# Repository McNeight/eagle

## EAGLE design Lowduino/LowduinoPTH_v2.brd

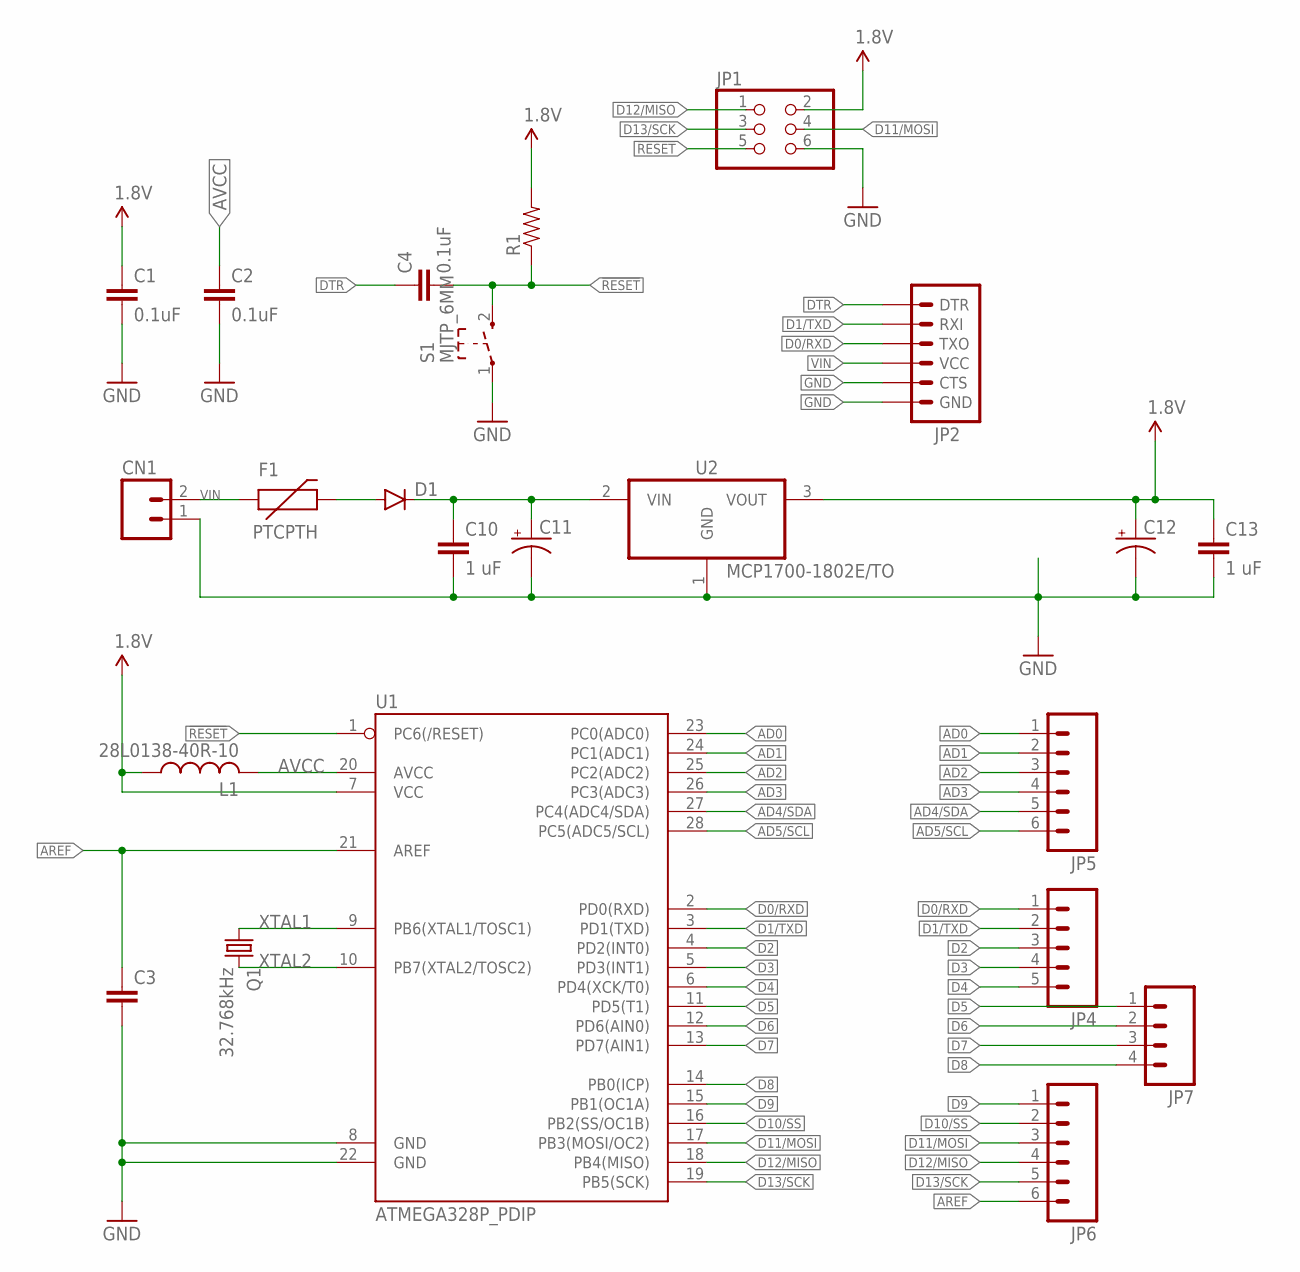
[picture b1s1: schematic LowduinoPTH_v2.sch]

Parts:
C1, C4: 0.1uF; CAP-PTH-SMALL
C2: 0.1uF; CAP-PTH-5MM
C3: CAPPTH; CAP-PTH-SMALL
C10, C13: 1 uF; CAP-PTH-SMALL
C11, C12: CPOL-USE2.5-6; E2,5-6
CN1: M02JST-PTH-VERT; JST-2-PTH-VERT
D1: DIODEPTH; DIODE-1N4001
F1: PTCPTH; PTC
JP1: PINHD-2X3; 2X03
JP2: ARDUINO_SERIAL_PROGRAMPTH; 1X06
JP4: M05NO_SILK; 1X05_NO_SILK
JP5, JP6: M06NO_SILK_FEMALE_PTH; 1X06_NO_SILK
JP7: M04NO_SILK_ALL_ROUND; 1X04_NO_SILK_ALL_ROUND
L1: 28L0138-40R-10; LAL03
Q1: 32.768kHz; TC26V
R1: RESISTORPTH-1/4W-VERT; AXIAL-0.1
S1: MJTP_6MM; MJTP1243
U1: ATMEGA328P_PDIP; DIL28-3
U2: MCP1700-1802E/TO; MICROCHIP_TO

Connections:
1.8V: C1.1, C12.+, C13.1, JP1.2, L1.1, R1.P$2 (2), U1.7 (VCC), U2.3 (VOUT)
!RESET: C4.2, JP1.5, R1.P$1 (1), S1.2 (3), U1.1 (PC6(/RESET))
AD0: JP5.1, U1.23 (PC0(ADC0))
AD1: JP5.2, U1.24 (PC1(ADC1))
AD2: JP5.3, U1.25 (PC2(ADC2))
AD3: JP5.4, U1.26 (PC3(ADC3))
AD4/SDA: JP5.5, U1.27 (PC4(ADC4/SDA))
AD5/SCL: JP5.6, U1.28 (PC5(ADC5/SCL))
AREF: C3.1, JP6.6, U1.21 (AREF)
AVCC: C2.1, L1.2, U1.20 (AVCC)
D0/RXD: JP2.3 (TXO), JP4.1, U1.2 (PD0(RXD))
D1/TXD: JP2.2 (RXI), JP4.2, U1.3 (PD1(TXD))
D2: JP4.3, U1.4 (PD2(INT0))
D3: JP4.4, U1.5 (PD3(INT1))
D4: JP4.5, U1.6 (PD4(XCK/T0))
D5: JP7.1, U1.11 (PD5(T1))
D6: JP7.2, U1.12 (PD6(AIN0))
D7: JP7.3, U1.13 (PD7(AIN1))
D8: JP7.4, U1.14 (PB0(ICP))
D9: JP6.1, U1.15 (PB1(OC1A))
D10/SS: JP6.2, U1.16 (PB2(SS/OC1B))
D11/MOSI: JP1.4, JP6.3, U1.17 (PB3(MOSI/OC2))
D12/MISO: JP1.1, JP6.4, U1.18 (PB4(MISO))
D13/SCK: JP1.3, JP6.5, U1.19 (PB5(SCK))
DTR: C4.1, JP2.1 (DTR)
GND: C1.2, C2.2, C3.2, C10.2, C11.-, C12.-, C13.2, CN1.1, JP1.6, JP2.5 (CTS), JP2.6 (GND), S1.1, U1.8 (GND), U1.22 (GND), U2.1 (GND)
unnamed: D1.A, F1.P$2 (2)
unnamed: C10.1, C11.+, D1.C, U2.2 (VIN)
VIN: CN1.2, F1.P$1 (1), JP2.4 (VCC)
XTAL1: Q1.1, U1.9 (PB6(XTAL1/TOSC1))
XTAL2: Q1.2, U1.10 (PB7(XTAL2/TOSC2))

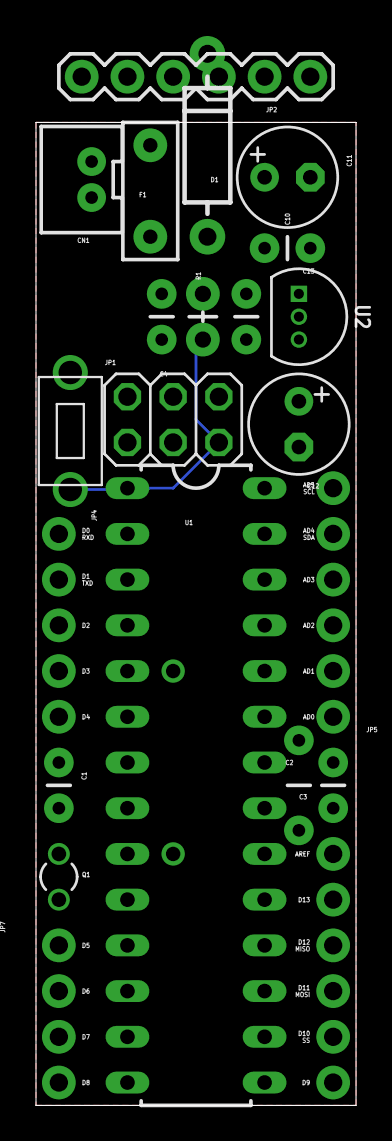
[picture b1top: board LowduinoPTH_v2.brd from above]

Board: 2 copper layers, 17.8 x 54.6 mm, 23 parts (1 on the bottom side), 31 nets.

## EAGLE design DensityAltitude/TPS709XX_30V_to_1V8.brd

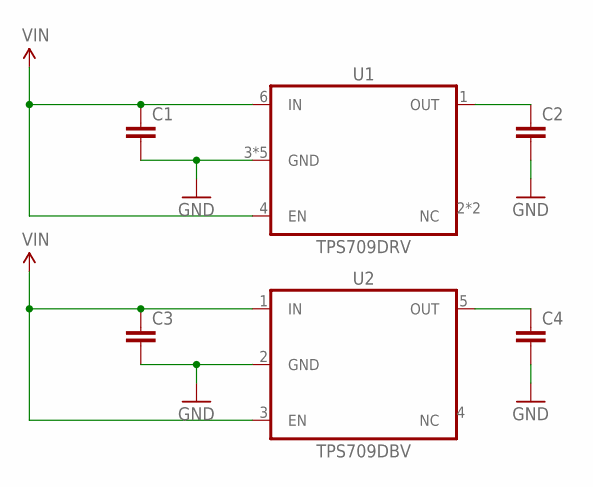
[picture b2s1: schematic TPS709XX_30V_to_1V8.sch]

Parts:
C1, C2: C-EUC0402; C0402
C3, C4: C-EUC0603; C0603
U1: TPS709DRV; DRV
U2: TPS709DBV; DBV

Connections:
GND: C1.2, C2.2, C3.2, C4.2, U1.3 (GND), U1.7 (GND), U1.8 (GND), U1.V1 (GND), U1.V2 (GND), U2.2 (GND)
VIN: C1.1, C3.1, U1.4 (EN), U1.6 (IN), U2.1 (IN), U2.3 (EN)
VOUT1: C2.1, U1.1 (OUT)
VOUT2: C4.1, U2.5 (OUT)

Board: 2 copper layers, 6 parts (0 on the bottom side), 4 nets, no tracks yet.

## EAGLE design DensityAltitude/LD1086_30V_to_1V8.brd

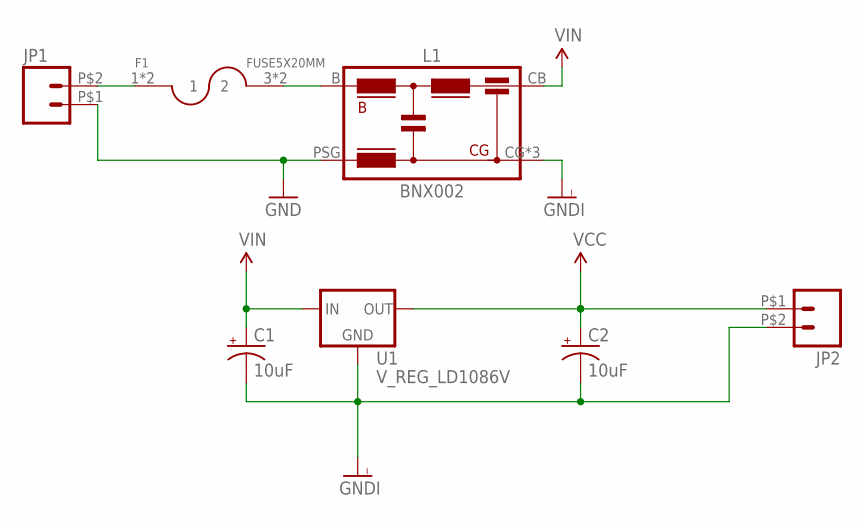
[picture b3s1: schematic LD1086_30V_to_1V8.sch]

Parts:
C1, C2: 10uF; KEMET_E
F1: FUSE5X20MM; FUSE_1A3399
JP1, JP2: M02TE-282834-2; 1X02_282834-2
L1: BNX002
U1: V_REG_LD1086V; TO-220-SINGLE

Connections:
GND: JP1.P$1 (1), L1.PSG
GNDI: C1.-, C2.-, JP2.P$2 (2), L1.CG, L1.CG1 (CG), L1.CG2 (CG), U1.GND
unnamed: F1.3 (2), F1.4 (2), L1.B
unnamed: F1.1, F1.2 (1), JP1.P$2 (2)
VCC: C2.+, JP2.P$1 (1), U1.OUT
VIN: C1.+, L1.CB, U1.IN

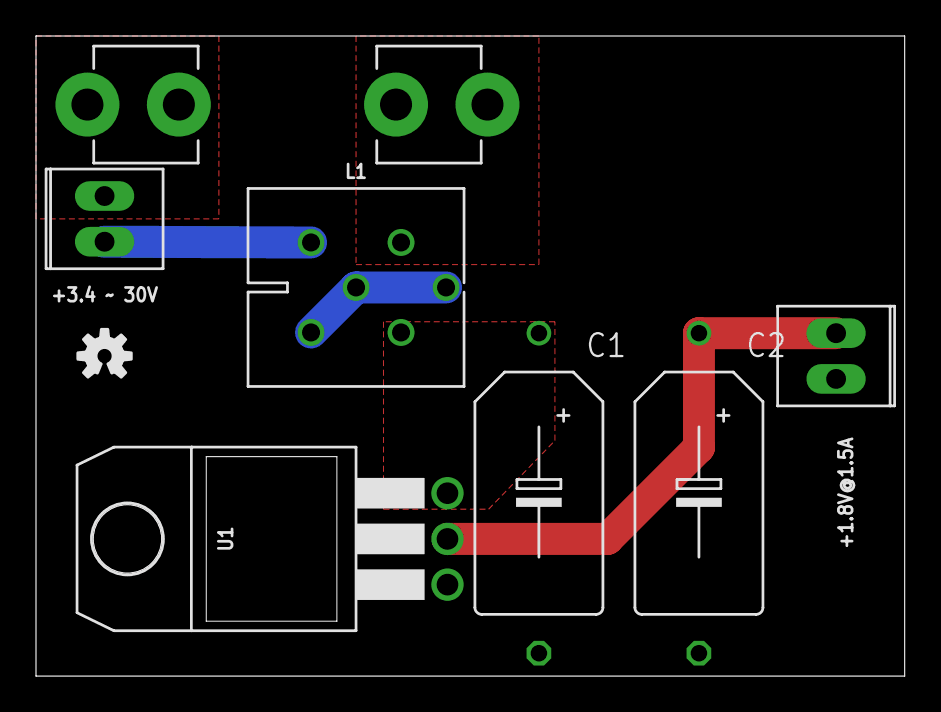
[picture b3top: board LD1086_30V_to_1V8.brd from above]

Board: 2 copper layers, 48.3 x 35.6 mm, 8 parts (0 on the bottom side), 6 nets.

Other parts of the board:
U$1: OSHW-LOGO-S

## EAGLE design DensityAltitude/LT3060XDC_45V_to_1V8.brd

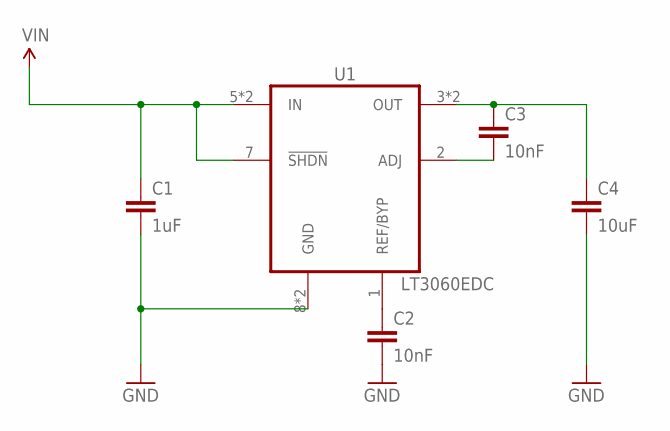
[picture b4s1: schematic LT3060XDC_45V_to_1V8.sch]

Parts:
C1: 1uF; C0402
C2, C3: 10nF; C0402
C4: 10uF; C0402
U1: LT3060EDC; LINEAR_DC8

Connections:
GND: C1.2, C2.2, C4.2, U1.8 (GND), U1.9 (GND)
unnamed: C3.2, U1.2 (ADJ)
unnamed: C2.1, U1.1 (REF/BYP)
OUT: C3.1, C4.1, U1.3 (OUT), U1.4 (OUT)
VIN: C1.1, U1.5 (IN), U1.6 (IN), U1.7 (!SHDN)

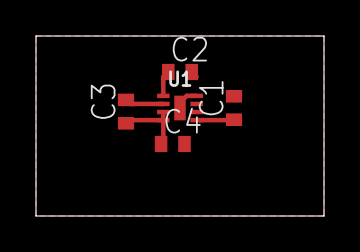
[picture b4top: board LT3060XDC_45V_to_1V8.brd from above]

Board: 2 copper layers, 16.0 x 10.0 mm, 5 parts (0 on the bottom side), 5 nets.

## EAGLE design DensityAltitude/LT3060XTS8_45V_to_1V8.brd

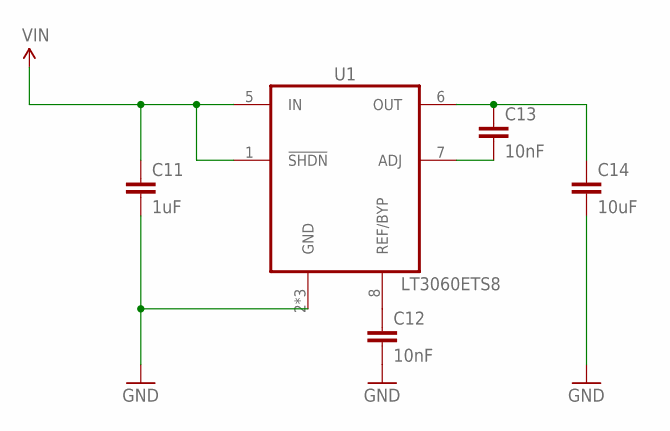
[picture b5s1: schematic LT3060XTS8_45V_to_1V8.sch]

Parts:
C11: 1uF; C0402
C12, C13: 10nF; C0402
C14: 10uF; C0402
U1: LT3060ETS8; LINEAR_TS8

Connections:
GND: C11.2, C12.2, C14.2, U1.2 (GND), U1.3 (GND), U1.4 (GND)
unnamed: C13.2, U1.7 (ADJ)
unnamed: C12.1, U1.8 (REF/BYP)
OUT: C13.1, C14.1, U1.6 (OUT)
VIN: C11.1, U1.1 (!SHDN), U1.5 (IN)

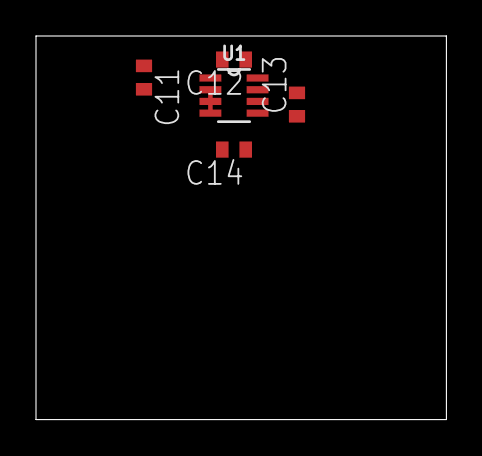
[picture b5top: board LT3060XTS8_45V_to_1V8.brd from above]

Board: 2 copper layers, 22.8 x 21.3 mm, 5 parts (0 on the bottom side), 5 nets.

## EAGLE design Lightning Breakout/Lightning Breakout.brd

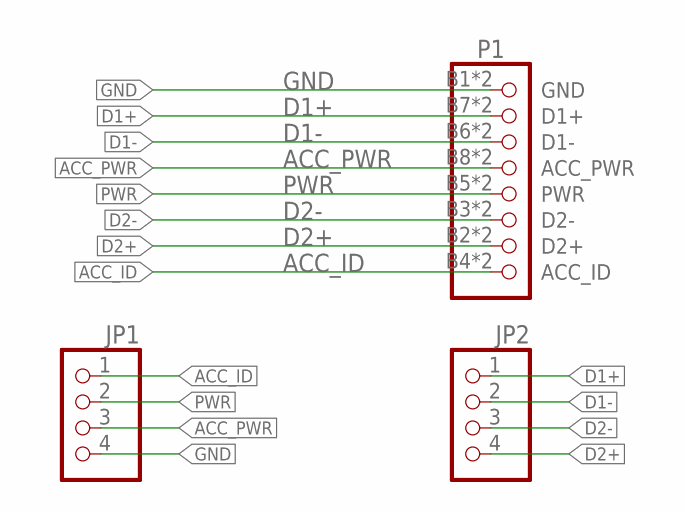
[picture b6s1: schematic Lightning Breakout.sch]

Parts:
JP1, JP2: PINHD-1X4; 1X04
P1: LIGHTNING-8PIN; LIGHTNING

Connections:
ACC_ID: JP1.1, P1.B4 (ACC_ID), P1.T8 (ACC_ID)
ACC_PWR: JP1.3, P1.B8 (ACC_PWR), P1.T4 (ACC_PWR)
D1+: JP2.1, P1.B7 (D1+), P1.T2 (D1+)
D1-: JP2.2, P1.B6 (D1-), P1.T3 (D1-)
D2+: JP2.4, P1.B2 (D2+), P1.T7 (D2+)
D2-: JP2.3, P1.B3 (D2-), P1.T6 (D2-)
GND: JP1.4, P1.B1 (GND), P1.T1 (GND)
PWR: JP1.2, P1.B5 (PWR), P1.T5 (PWR)

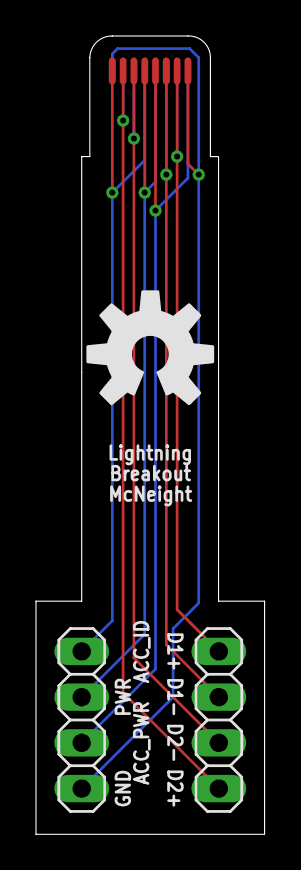
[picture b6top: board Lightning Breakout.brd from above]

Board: 2 copper layers, 12.7 x 44.4 mm, 4 parts (0 on the bottom side), 8 nets.

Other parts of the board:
U$1: OSHW-LOGO-L

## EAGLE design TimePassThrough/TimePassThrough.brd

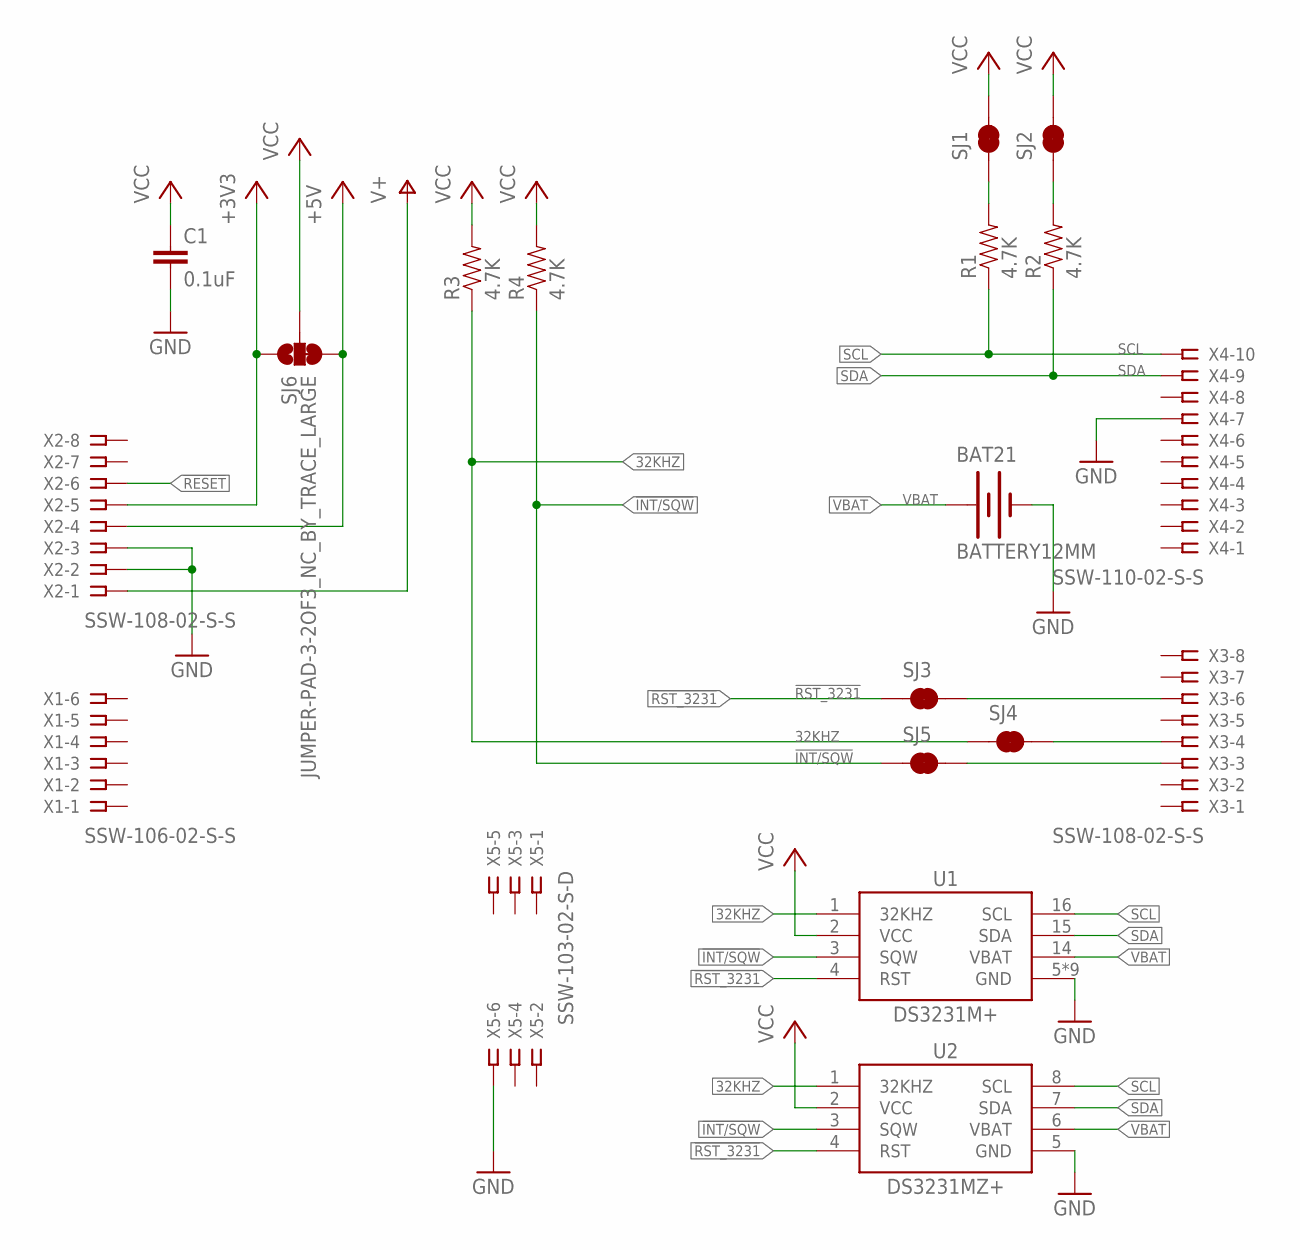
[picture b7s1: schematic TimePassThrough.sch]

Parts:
BAT21: BATTERY12MM; BATTCON_12MM
C1: 0.1uF; 0805
R1, R2, R3, R4: 4.7K; 0805
SJ1, SJ2, SJ3, SJ4, SJ5: JUMPER-PAD-2-NC_BY_TRACE; PAD-JUMPER-2-NC_BY_TRACE_YES_SILK
SJ6: JUMPER-PAD-3-2OF3_NC_BY_TRACE_LARGE; PAD-JUMPER-3-2OF3_NC_BY_TRACE_YES_SILK_LARGE
U1: DS3231M+; W16MK+1
U2: DS3231MZ+; S8MK+1
X1: SSW-106-02-S-S
X2, X3: SSW-108-02-S-S
X4: SSW-110-02-S-S
X5: SSW-103-02-S-D

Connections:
32KHZ: R3.1, SJ4.1, U1.1 (32KHZ), U2.1 (32KHZ)
!INT/SQW: R4.1, SJ5.1, U1.3 (SQW), U2.3 (SQW)
!RESET: X2.6
!RST_3231: SJ3.1, U1.4 (RST), U2.4 (RST)
+3V3: SJ6.1, X2.5
+5V: SJ6.3, X2.4
GND: BAT21.GND (-), C1.2, U1.5 (GND), U1.6 (GND), U1.7 (GND), U1.8 (GND), U1.9 (GND), U1.10 (GND), U1.11 (GND), U1.12 (GND), U1.13 (GND), U2.5 (GND), X2.2, X2.3, X4.7, X5.6
unnamed: SJ3.2, X3.6
unnamed: SJ4.2, X3.4
unnamed: SJ5.2, X3.3
unnamed: R1.2, SJ1.1
unnamed: R2.2, SJ2.1
SCL: R1.1, U1.16 (SCL), U2.8 (SCL), X4.10
SDA: R2.1, U1.15 (SDA), U2.7 (SDA), X4.9
V+: X2.1
VBAT: BAT21.PWR@1 (+), BAT21.PWR@2 (+), U1.14 (VBAT), U2.6 (VBAT)
VCC: C1.1, R3.2, R4.2, SJ1.2, SJ2.2, SJ6.2, U1.2 (VCC), U2.2 (VCC)

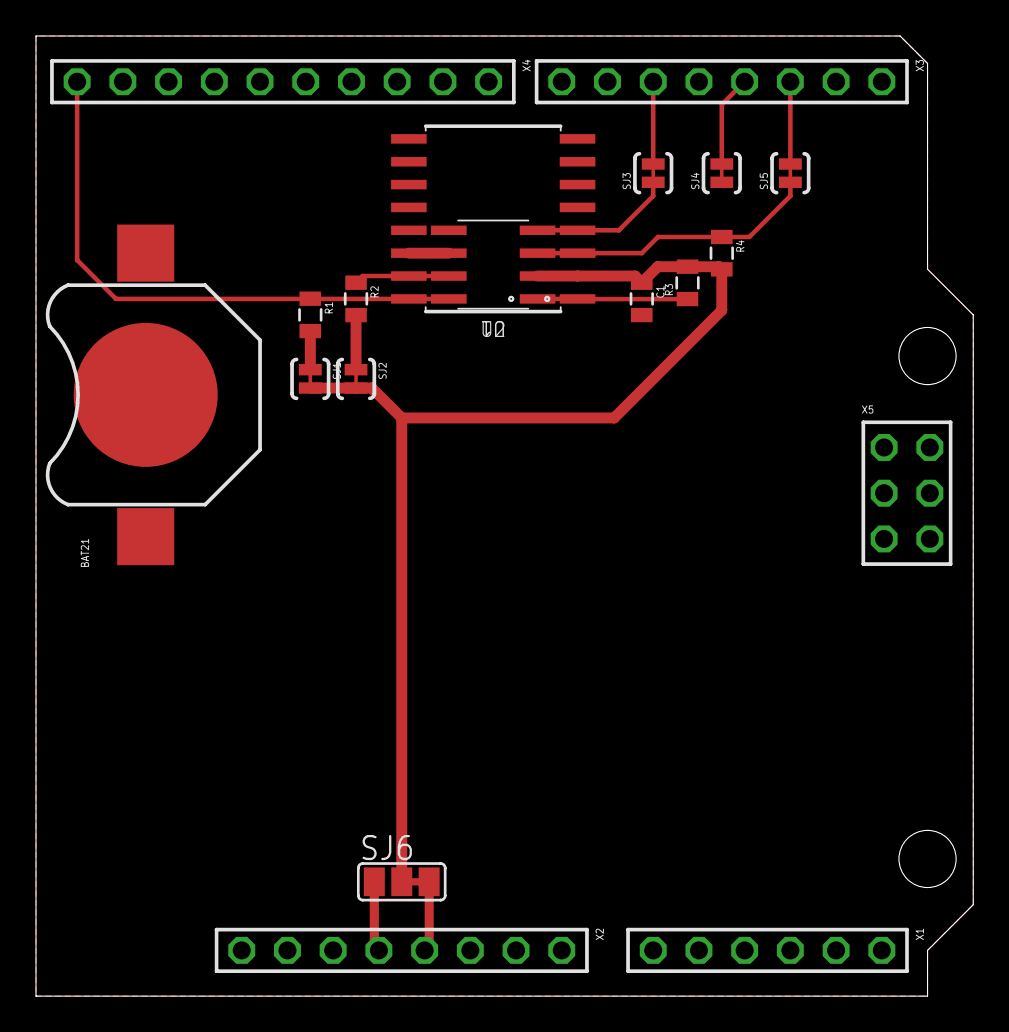
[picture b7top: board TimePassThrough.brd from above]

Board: 2 copper layers, 52.1 x 53.3 mm, 19 parts (0 on the bottom side), 15 nets.

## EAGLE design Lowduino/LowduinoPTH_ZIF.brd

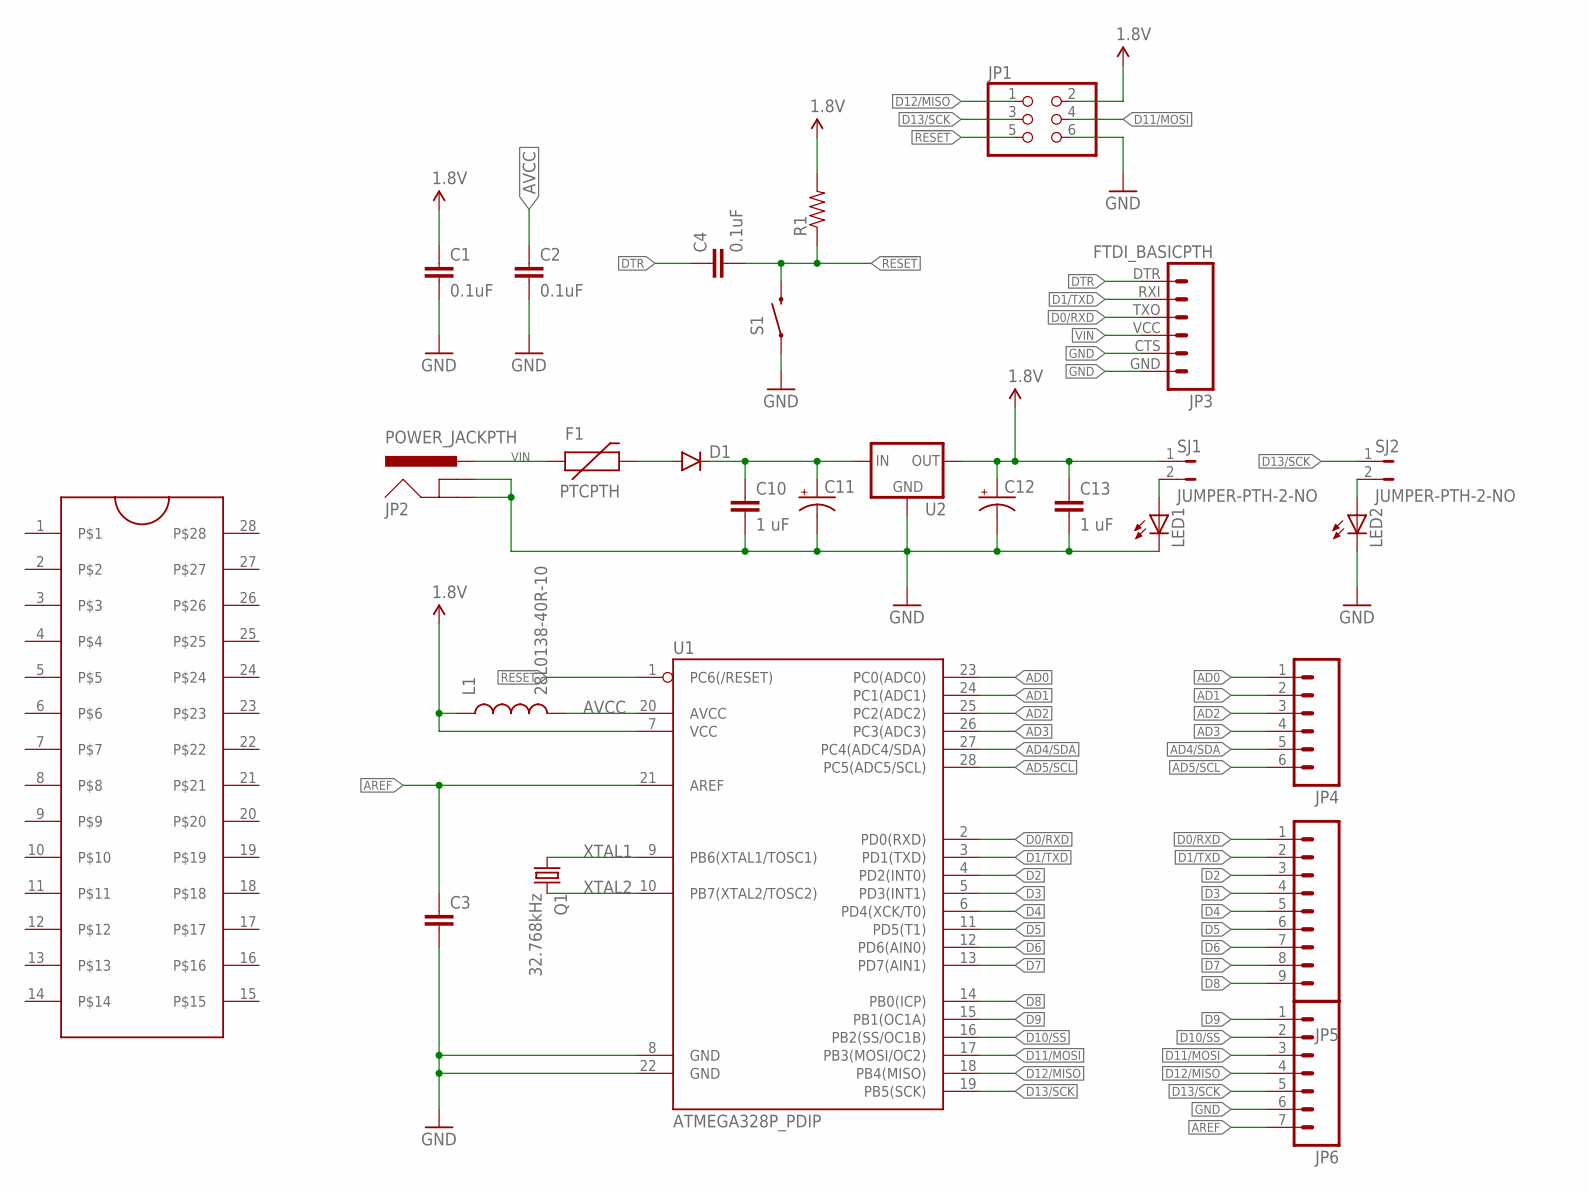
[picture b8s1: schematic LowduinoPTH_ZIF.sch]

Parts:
C1, C4: 0.1uF; CAP-PTH-SMALL2
C2: 0.1uF; CAP-PTH-5MM
C3: CAPPTH2; CAP-PTH-SMALL2
C10, C13: 1 uF; CAP-PTH-SMALL2
C11, C12: CPOL-USE2.5-6; E2,5-6
D1: DIODEPTH; DIODE-1N4001
F1: PTCPTH; PTC
JP1: PINHD-2X3; 2X03
JP2: POWER_JACKPTH; POWER_JACK_PTH
JP3: FTDI_BASICPTH; FTDI_BASIC
JP4: M06SILK_FEMALE_PTH; 1X06
JP5: M09; 1X09
JP6: M07; 1X07
L1: 28L0138-40R-10; AXIAL-0.6
LED1, LED2: LED3MM
Q1: 32.768kHz; TC26V
R1: RESISTORPTH-1/4W-VERT; AXIAL-0.1
S1: SWITCH-MOMENTARY-2PTH; TACTILE-PTH
SJ1, SJ2: JUMPER-PTH-2-NO; PTH-JUMPER-2-NO_NO_SILK
U1: ATMEGA328P_PDIP; DIL28-3
U2: V_REG_78XXTO-92_UNTESTED; TO-92
U$1: ZIFSOCKET-28-3ZIFFSOCKET-28-3; DIL28-3-ZIF_SOCKET

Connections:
1.8V: C1.1, C12.+, C13.1, JP1.2, L1.P$1 (1), R1.P$2 (2), SJ1.1, U1.7 (VCC), U2.3 (OUT)
!RESET: C4.2, JP1.5, R1.P$1 (1), S1.3 (2), U1.1 (PC6(/RESET))
AD0: JP4.1, U1.23 (PC0(ADC0))
AD1: JP4.2, U1.24 (PC1(ADC1))
AD2: JP4.3, U1.25 (PC2(ADC2))
AD3: JP4.4, U1.26 (PC3(ADC3))
AD4/SDA: JP4.5, U1.27 (PC4(ADC4/SDA))
AD5/SCL: JP4.6, U1.28 (PC5(ADC5/SCL))
AREF: C3.1, JP6.7, U1.21 (AREF)
AVCC: C2.1, L1.P$2 (2), U1.20 (AVCC)
D0/RXD: JP3.TXO (3), JP5.1, U1.2 (PD0(RXD))
D1/TXD: JP3.RXI (2), JP5.2, U1.3 (PD1(TXD))
D2: JP5.3, U1.4 (PD2(INT0))
D3: JP5.4, U1.5 (PD3(INT1))
D4: JP5.5, U1.6 (PD4(XCK/T0))
D5: JP5.6, U1.11 (PD5(T1))
D6: JP5.7, U1.12 (PD6(AIN0))
D7: JP5.8, U1.13 (PD7(AIN1))
D8: JP5.9, U1.14 (PB0(ICP))
D9: JP6.1, U1.15 (PB1(OC1A))
D10/SS: JP6.2, U1.16 (PB2(SS/OC1B))
D11/MOSI: JP1.4, JP6.3, U1.17 (PB3(MOSI/OC2))
D12/MISO: JP1.1, JP6.4, U1.18 (PB4(MISO))
D13/SCK: JP1.3, JP6.5, SJ2.1, U1.19 (PB5(SCK))
DTR: C4.1, JP3.DTR (1)
GND: C1.2, C2.2, C3.2, C10.2, C11.-, C12.-, C13.2, JP1.6, JP2.GND, JP2.GNDBREAK, JP3.CTS (5), JP3.GND (6), JP6.6, LED1.K (C), LED2.K (C), S1.1, U1.8 (GND), U1.22 (GND), U2.1 (GND)
unnamed: LED1.A, SJ1.2
unnamed: LED2.A, SJ2.2
unnamed: D1.A, F1.P$2 (2)
unnamed: C10.1, C11.+, D1.C, U2.2 (IN)
VIN: F1.P$1 (1), JP2.PWR, JP3.VCC (4)
XTAL1: Q1.1, U1.9 (PB6(XTAL1/TOSC1))
XTAL2: Q1.2, U1.10 (PB7(XTAL2/TOSC2))

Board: 2 copper layers, 27 parts (0 on the bottom side), 33 nets, no tracks yet.

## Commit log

2015-04-21 Versions Submitted to OSHPark 04 April 2015 - "LowduinoPTH_Take3.brd" as "Lowduino PTH" 18 April 2015 - "ATtiny20 Study.brd - UFBGA15.brd" as "ATtiny20 UFBGA Breakout Board" 21 April 2015 - "BME280_B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
2015-04-21 Miscelaneous libraries I've been working on
2015-04-21 Excluding directories of files from other sources
2015-04-21 Variations on an ATtiny20 breakout board
2015-04-21 Variations on an ATtiny43U breakout board
2015-04-21 Variations on an ATtiny85 breakout board
2015-04-21 Works in progress related to a density altitude gauge
2015-04-21 Various sketches and thought experiments
2015-04-21 Templates for an Arduino R3 compatible shield
2015-04-21 Idea for a half-scale Arduino
2015-04-21 Variations on an ATtiny167 breakout board
2015-04-21 Listing of keyboard shortcuts for Eagle CAD
2015-04-21 Works in progress for a "low and slow" Arduino
2015-04-21 Real time clock shield using Maxim DS3231M and passing through all connectors to shields above
2015-04-21 Merged single device in fx122.lbr into Lowduino.lbr
2015-04-23 Lightning Breakout submitted to OSHPark on 22 April 2015
2015-04-23 Moved 1V8 voltage regulators from DensityAltitude.lbr to 1V8.lbr More layout work for various high input voltage regulators A bit more work on LowduinoPTH_v2

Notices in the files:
parts and their libraries:
SparkFun-Aesthetics: Licensing: Creative Commons ShareAlike 4.0 International - https://creativecommons.org/licenses/by-sa/4.0
